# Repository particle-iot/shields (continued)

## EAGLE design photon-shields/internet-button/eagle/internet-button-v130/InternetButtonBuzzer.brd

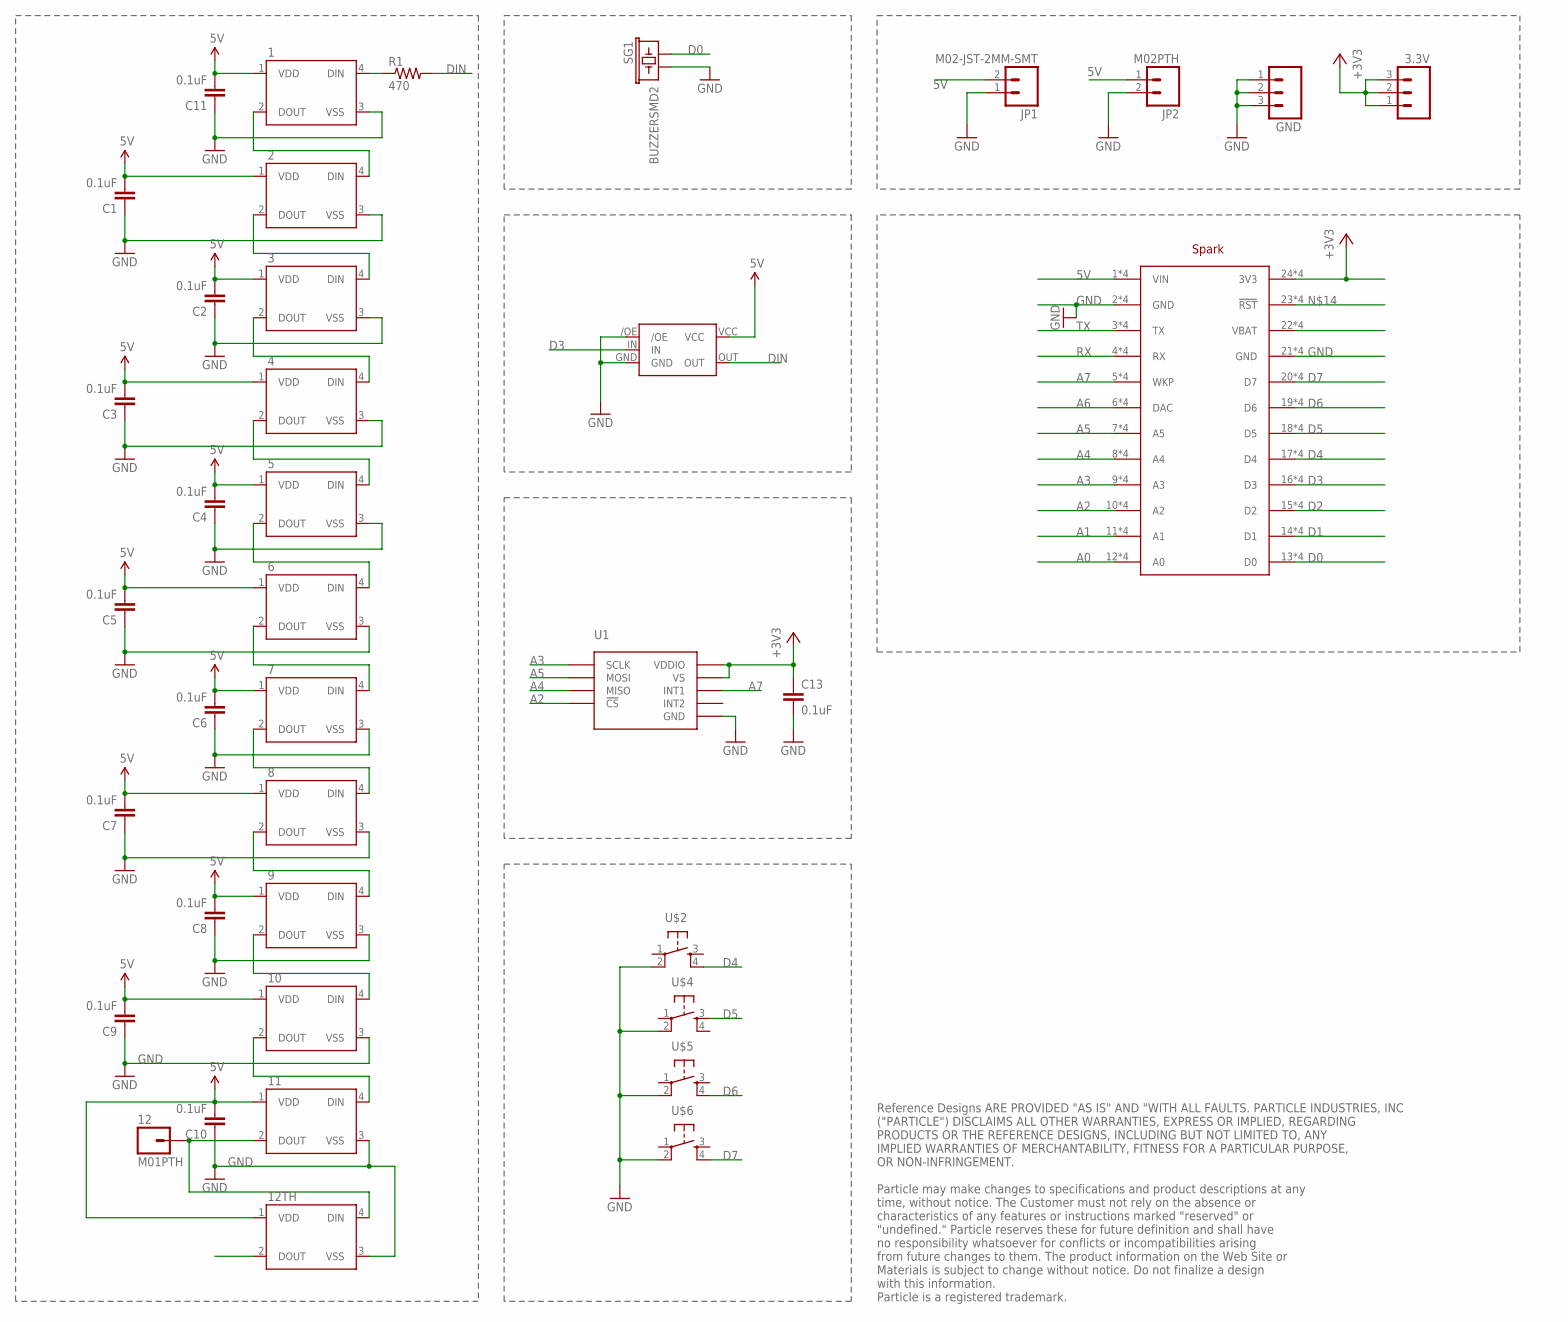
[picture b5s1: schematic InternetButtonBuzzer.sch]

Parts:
1, 2, 3, 4, 5, 6, 7, 8, 9, 10, 11: WS2812B
3.3V: M03LOCK_NO_SILK; 1X03_LOCK_NO_SILK
12: M01PTH; 1X01
12TH: WS2812B; NOCREAM_WS2812B
C1, C2, C3, C4, C5, C6, C7, C8, C9, C10, C11, C13: 0.1uF; 0603-CAP
GND: M03LOCK_NO_SILK; 1X03_LOCK_NO_SILK
JP1: M02-JST-2MM-SMT; JST-2-SMD
JP2: M02PTH; 1X02
R1: 470; 0603-RES
SG1: BUZZERSMD2; BUZZER-CCV
U1: ADXL362ADXL362-1:1; ADXL362-1:1
U$2, U$4, U$5, U$6: 12MM_TACTILE_SWITCH
U$3: SPARK_LOGO_WITH_PLANE; SPARK_LOGO_PLUS_PLANE
U$7: SPARK_COREDUAL_HEADER; SPARK_CORE_DUAL_HEADER
U$8: NL17SZ125SOT553; SOT-553

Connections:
5V: 1.1 (VDD), 2.1 (VDD), 3.1 (VDD), 4.1 (VDD), 5.1 (VDD), 6.1 (VDD), 7.1 (VDD), 8.1 (VDD), 9.1 (VDD), 10.1 (VDD), 11.1 (VDD), 12TH.1 (VDD), C1.2, C2.2, C3.2, C4.2, C5.2, C6.2, C7.2, C8.2, C9.2, C10.2, C11.2, JP1.2 (1), JP2.1, U$7.1 (VIN), U$7.1B (VIN), U$7.@1 (VIN), U$7.@1B (VIN), U$8.VCC
+3V3: 3.3V.1, 3.3V.2, 3.3V.3, C13.1, U1.P$1 (VDDIO), U1.P$14 (VS), U$7.24 (3V3), U$7.24B (3V3), U$7.@24 (3V3), U$7.@24B (3V3)
A0: U$7.12 (A0), U$7.12B (A0), U$7.@12 (A0), U$7.@12B (A0)
A1: U$7.11 (A1), U$7.11B (A1), U$7.@11 (A1), U$7.@11B (A1)
A2: U1.P$8 (!CS), U$7.10 (A2), U$7.10B (A2), U$7.@10 (A2), U$7.@10B (A2)
A3: U1.P$4 (SCLK), U$7.9 (A3), U$7.9B (A3), U$7.@9 (A3), U$7.@9B (A3)
A4: U1.P$7 (MISO), U$7.8 (A4), U$7.8B (A4), U$7.@8 (A4), U$7.@8B (A4)
A5: U1.P$6 (MOSI), U$7.7 (A5), U$7.7B (A5), U$7.@7 (A5), U$7.@7B (A5)
A6: U$7.6 (DAC), U$7.6B (DAC), U$7.@6 (DAC), U$7.@6B (DAC)
A7: U1.P$11 (INT1), U$7.5 (WKP), U$7.5B (WKP), U$7.@5 (WKP), U$7.@5B (WKP)
D0: SG1.+ (1), U$7.13 (D0), U$7.13B (D0), U$7.@13 (D0), U$7.@13B (D0)
D1: U$7.14 (D1), U$7.14B (D1), U$7.@14 (D1), U$7.@14B (D1)
D2: U$7.15 (D2), U$7.15B (D2), U$7.@15 (D2), U$7.@15B (D2)
D3: U$7.16 (D3), U$7.16B (D3), U$7.@16 (D3), U$7.@16B (D3), U$8.IN
D4: U$2.4, U$7.17 (D4), U$7.17B (D4), U$7.@17 (D4), U$7.@17B (D4)
D5: U$4.3, U$7.18 (D5), U$7.18B (D5), U$7.@18 (D5), U$7.@18B (D5)
D6: U$5.4, U$7.19 (D6), U$7.19B (D6), U$7.@19 (D6), U$7.@19B (D6)
D7: U$6.4, U$7.20 (D7), U$7.20B (D7), U$7.@20 (D7), U$7.@20B (D7)
DIN: R1.2, U$8.OUT
GND: 1.3 (VSS), 2.3 (VSS), 3.3 (VSS), 4.3 (VSS), 5.3 (VSS), 6.3 (VSS), 7.3 (VSS), 8.3 (VSS), 9.3 (VSS), 10.3 (VSS), 11.3 (VSS), 12TH.3 (VSS), C1.1, C2.1, C3.1, C4.1, C5.1, C6.1, C7.1, C8.1, C9.1, C10.1, C11.1, C13.2, GND.1, GND.2, GND.3, JP1.1 (2), JP2.2, SG1.- (2), U1.P$12 (GND), U1.P$13 (GND), U1.P$16 (GND), U$2.2, U$4.2, U$5.2, U$6.2, U$7.2 (GND), U$7.2B (GND), U$7.21 (GND), U$7.21B (GND), U$7.@2 (GND), U$7.@2B (GND), U$7.@21 (GND), U$7.@21B (GND), U$8./OE, U$8.GND
unnamed: 2.2 (DOUT), 3.4 (DIN)
unnamed: 3.2 (DOUT), 4.4 (DIN)
unnamed: 11.2 (DOUT), 12.1, 12TH.4 (DIN)
unnamed: 7.2 (DOUT), 8.4 (DIN)
unnamed: 8.2 (DOUT), 9.4 (DIN)
unnamed: 9.2 (DOUT), 10.4 (DIN)
unnamed: 10.2 (DOUT), 11.4 (DIN)
unnamed: U$7.23 (!RST), U$7.23B (!RST), U$7.@23 (!RST), U$7.@23B (!RST)
unnamed: U$7.22 (VBAT), U$7.22B (VBAT), U$7.@22 (VBAT), U$7.@22B (VBAT)
unnamed: 1.4 (DIN), R1.1
unnamed: 4.2 (DOUT), 5.4 (DIN)
unnamed: 5.2 (DOUT), 6.4 (DIN)
unnamed: 6.2 (DOUT), 7.4 (DIN)
unnamed: 1.2 (DOUT), 2.4 (DIN)
RX: U$7.4 (RX), U$7.4B (RX), U$7.@4 (RX), U$7.@4B (RX)
TX: U$7.3 (TX), U$7.3B (TX), U$7.@3 (TX), U$7.@3B (TX)

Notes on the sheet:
Reference Designs ARE PROVIDED "AS IS" AND "WITH ALL FAULTS. PARTICLE INDUSTRIES, INC ("PARTICLE") DISCLAIMS ALL OTHER WARRANTIES, EXPRESS OR IMPLIED, REGARDING PRODUCTS OR THE REFERENCE DESIGNS, INCLUDING BUT NOT LIMITED TO, ANY IMPLIED WARRANTIES OF MERCHANTABILITY, FITNESS FOR A PARTICULAR PURPO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

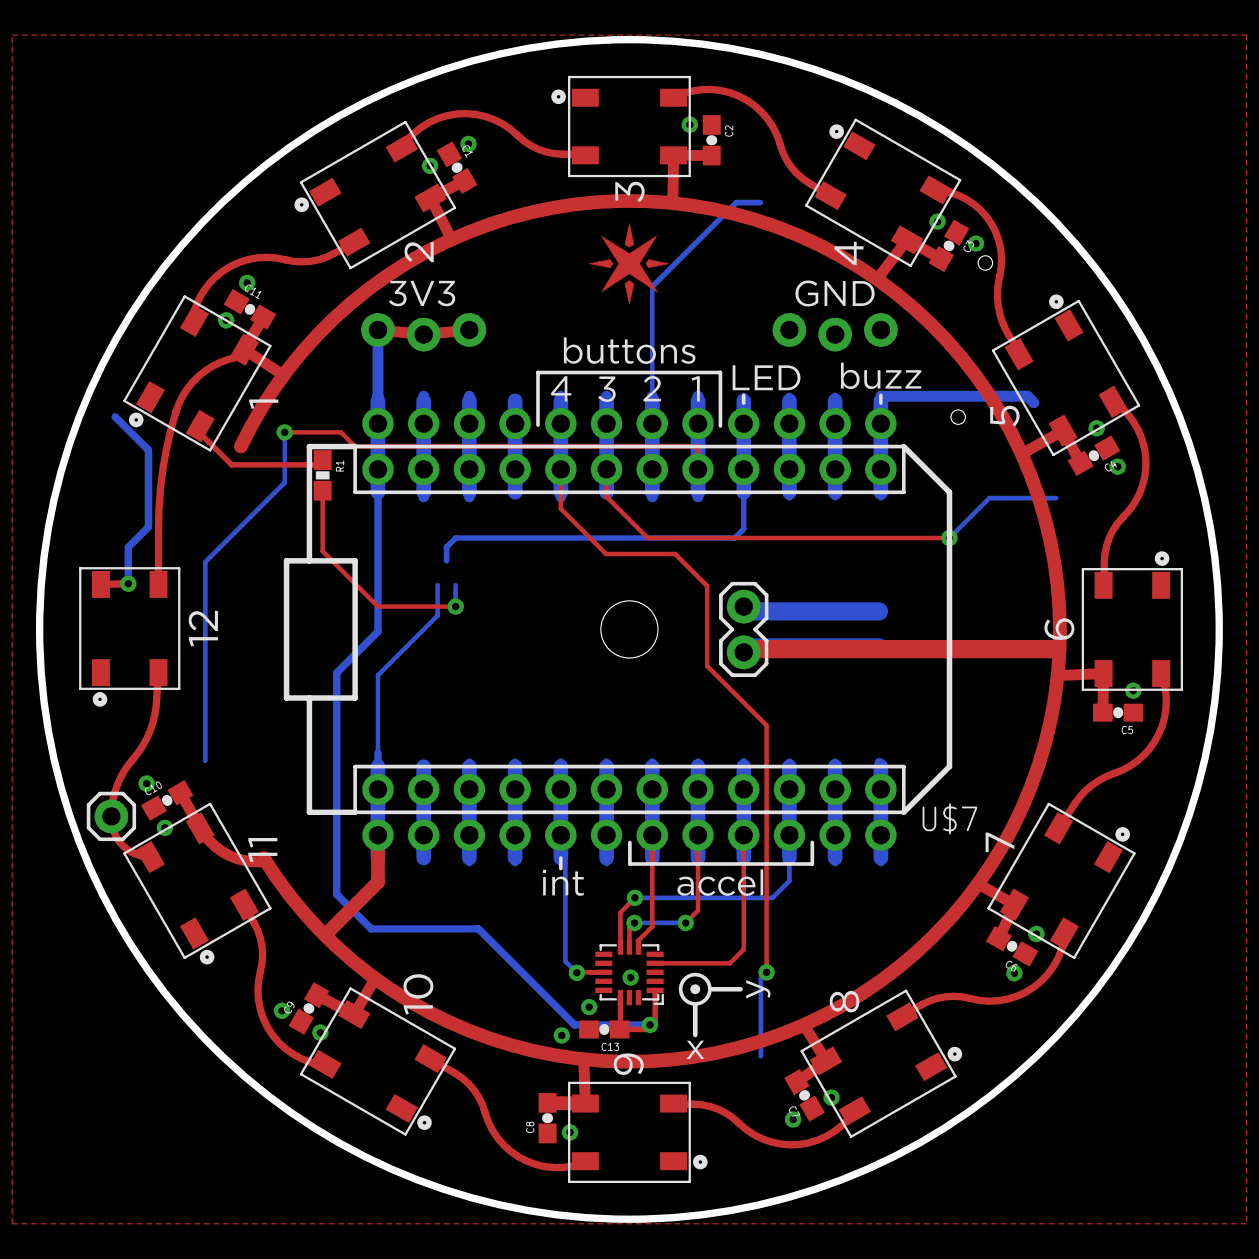
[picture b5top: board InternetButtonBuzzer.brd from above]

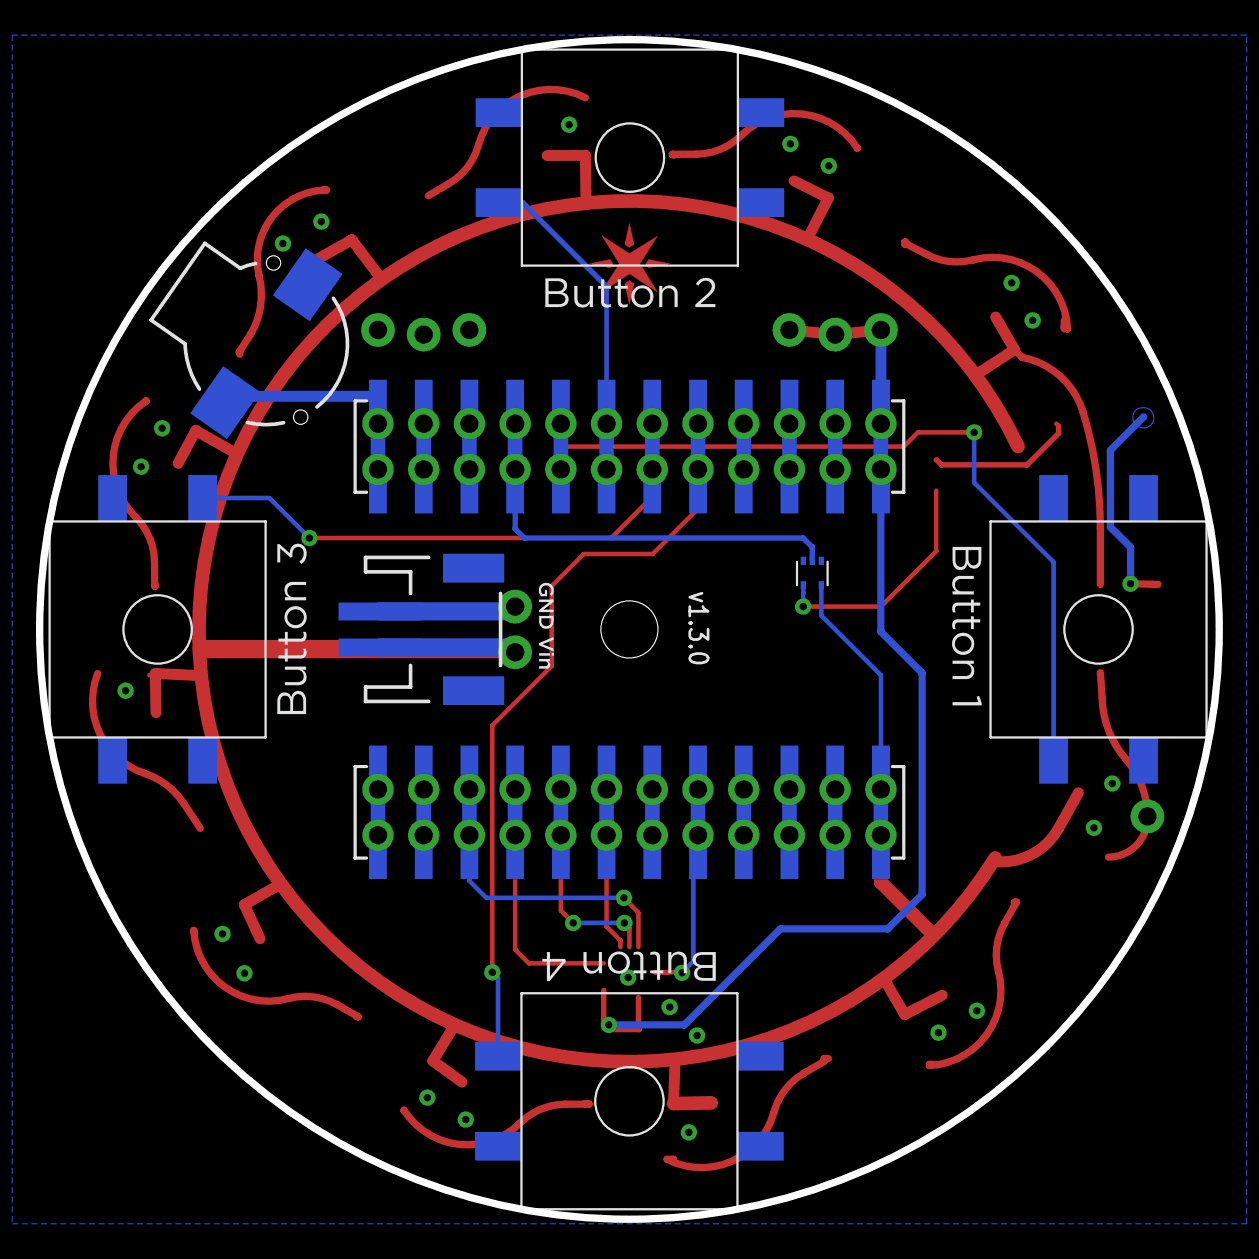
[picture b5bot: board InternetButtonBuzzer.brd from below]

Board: 2 copper layers, 65.5 x 65.5 mm, 39 parts (7 on the bottom side), 36 nets.

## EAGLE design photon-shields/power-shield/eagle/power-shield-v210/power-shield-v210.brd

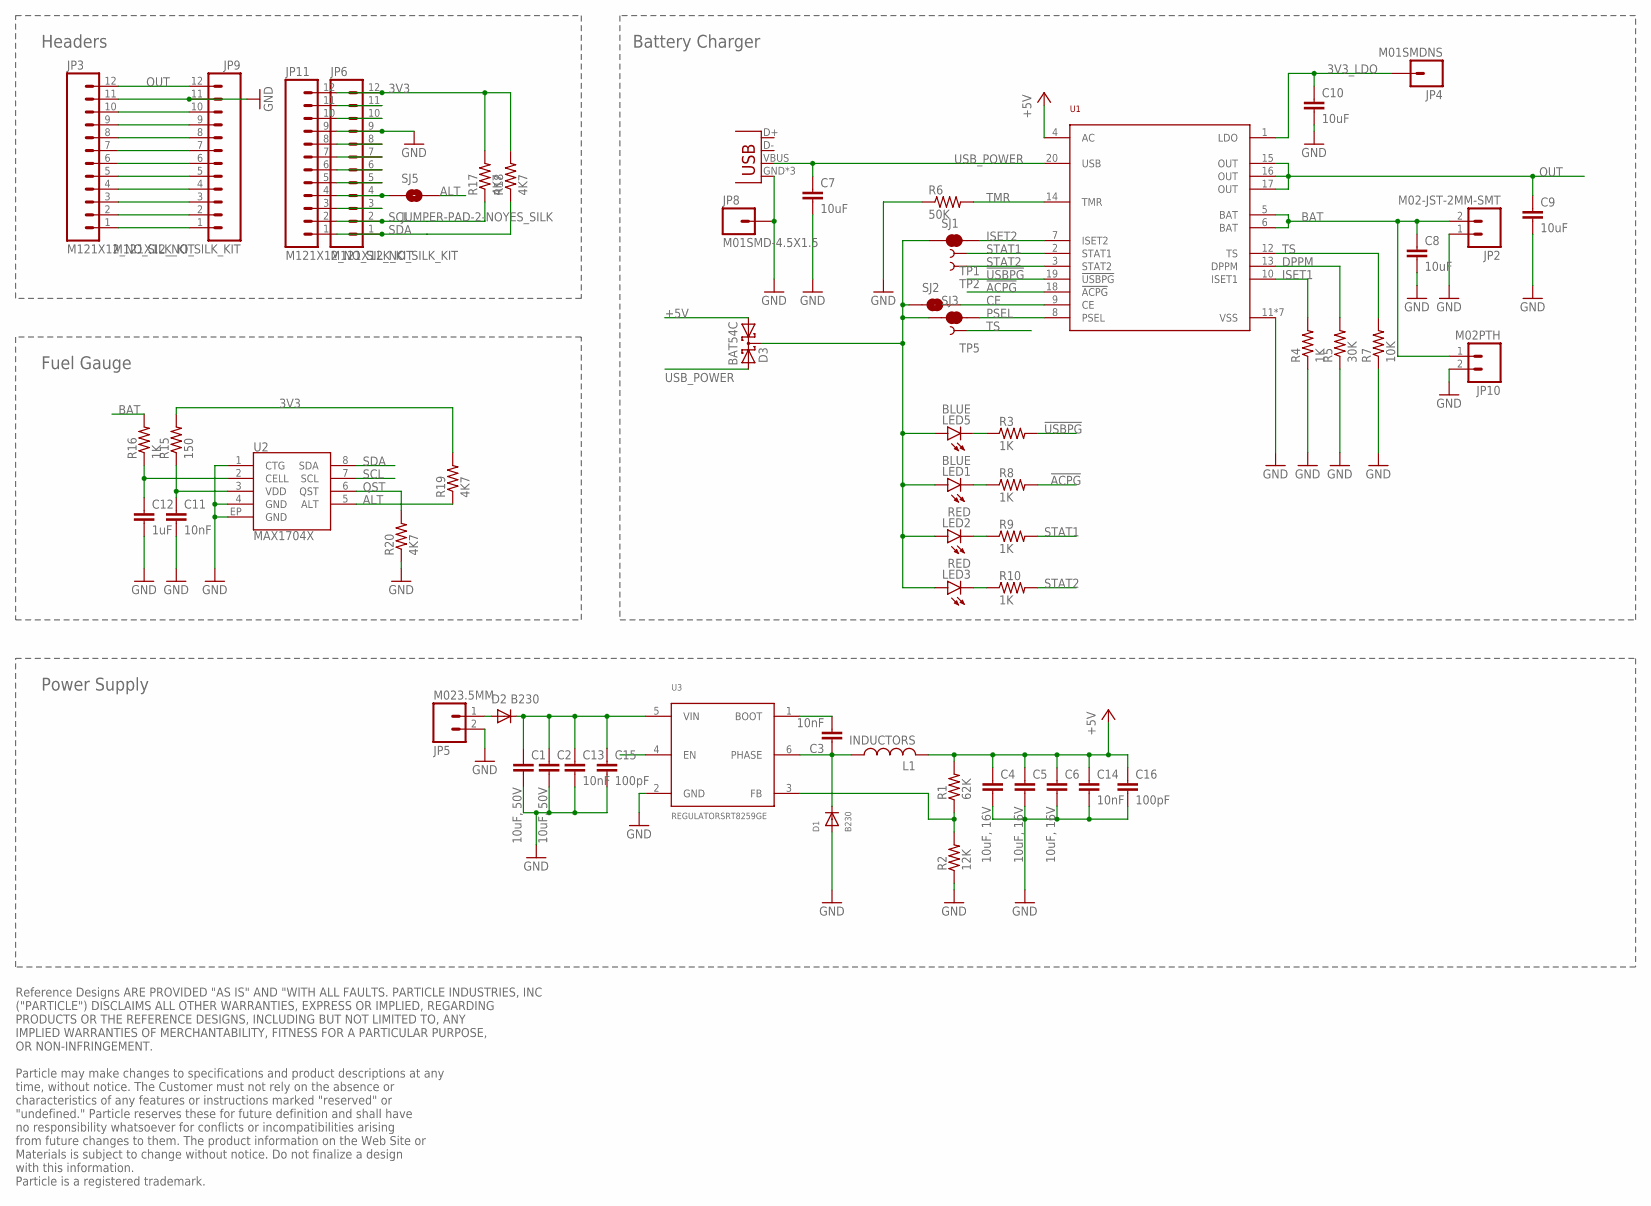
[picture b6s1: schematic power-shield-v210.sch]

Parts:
C1, C2: 10uF, 50V; 1206
C3, C11, C13, C14: 10nF; 0402-CAP
C4, C5, C6: 10uF, 16V; 1206
C7, C8, C9, C10: 10uF; 0603-CAP
C12: 1uF; 0402-CAP
C15, C16: 100pF; 0402-CAP
D1, D2: B230; SMADIODE
D3: BAT54C; SOT23
JP1: USBUSB-MICROB-SLOT-HOLE; USB-MICROB-SLOT-HOLE
JP2: M02-JST-2MM-SMT; JST-2-SMD
JP3, JP6, JP9, JP11: M121X12_NO_SILK_KIT; 1X12_NO_SILK_KIT
JP4: M01SMDNS; 1X01NS
JP5: M023.5MM; SCREWTERMINAL-3.5MM-2
JP8: M01SMD-4.5X1.5; PAD-1.5X4.5
JP10: M02PTH; 1X02
L1: INDUCTORS; NR8040T6R8N
LED1, LED5: BLUE; LED-0603
LED2, LED3: RED; LED-0603
R1: 62K; 0603-RES
R2: 12K; 0603-RES
R3, R4, R8, R9, R10: 1K; 0402-RES
R5: 30K; 0402-RES
R6: 50K; 0402-RES
R7: 10K; 0402-RES
R15: 150; 0603-RES
R16: 1K; 0603-RES
R17, R18, R19, R20: 4K7; 0402-RES
SJ1, SJ2, SJ3: JUMPER-PAD-2-NC_BY_TRACE; PAD-JUMPER-2-NC_BY_TRACE_YES_SILK
SJ5: JUMPER-PAD-2-NOYES_SILK; PAD-JUMPER-2-NO_YES_SILK
TP1, TP2, TP5: TEST-POINT3; PAD.03X.03
U1: BQ24030BQ24030; R-PVQFN-N20
U2: MAX1704X; TDFN-8
U3: REGULATORSRT8259GE; SOT23-6

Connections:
3V3: JP6.12, JP11.12, R15.2, R17.2, R18.2, R19.2
3V3_LDO: C10.1, JP4.1, U1.1 (LDO)
!ACPG: R8.2, U1.18 (!ACPG)
!USBPG: R3.2, U1.19 (!USBPG)
+5V: C4.1, C5.1, C6.1, C14.1, C16.1, D3.1 (A1), L1.P$2 (2), R1.2, U1.4 (AC)
ALT: R19.1, SJ5.2, U2.5 (ALT)
BAT: C8.1, JP2.2 (1), JP10.1, R16.2, U1.5 (BAT), U1.6 (BAT)
CE: SJ2.2, U1.9 (CE)
DPPM: R5.2, U1.13 (DPPM)
GND: C1.2, C2.2, C4.2, C5.2, C6.2, C7.2, C8.2, C9.2, C10.2, C11.2, C12.2, C13.2, C14.2, C15.2, C16.2, D1.A, JP1.GND, JP1.MT1 (GND), JP1.MT2 (GND), JP2.1 (2), JP3.11, JP5.2, JP6.9, JP8.P$1, JP9.11, JP10.2, JP11.9, R2.1, R4.1, R5.1, R6.1, R7.1, R20.1, U1.11 (VSS), U1.21 (VSS), U1.22 (VSS), U1.23 (VSS), U1.24 (VSS), U1.25 (VSS), U1.26 (VSS), U2.1 (CTG), U2.4 (GND), U2.EP (GND), U3.2 (GND)
ISET1: R4.2, U1.10 (ISET1)
ISET2: SJ1.2, U1.7 (ISET2)
unnamed: LED5.C, R3.1
unnamed: D3.3 (CC), LED1.A, LED2.A, LED3.A, LED5.A, SJ1.1, SJ2.1, SJ3.1
unnamed: LED3.C, R10.1
unnamed: LED2.C, R9.1
unnamed: LED1.C, R8.1
unnamed: JP6.4, JP11.4, SJ5.1
unnamed: JP3.1, JP9.1
unnamed: JP3.2, JP9.2
unnamed: JP3.3, JP9.3
unnamed: C12.1, R16.1, U2.2 (CELL)
unnamed: C11.1, R15.1, U2.3 (VDD)
unnamed: JP3.4, JP9.4
unnamed: C1.1, C2.1, C13.1, C15.1, D2.C, U3.5 (VIN)
unnamed: JP3.5, JP9.5
unnamed: JP3.6, JP9.6
unnamed: JP3.7, JP9.7
unnamed: JP3.8, JP9.8
unnamed: JP3.9, JP9.9
unnamed: JP3.10, JP9.10
unnamed: JP6.11, JP11.11
unnamed: JP6.10, JP11.10
unnamed: JP6.8, JP11.8
unnamed: JP6.7, JP11.7
unnamed: JP6.6, JP11.6
unnamed: JP6.5, JP11.5
unnamed: JP6.3, JP11.3
unnamed: D2.A, JP5.1
unnamed: C3.1, D1.C, L1.P$1 (1), U3.6 (PHASE)
unnamed: C3.2, U3.1 (BOOT)
unnamed: R1.1, R2.2, U3.3 (FB)
OUT: C9.1, JP3.12, JP9.12, U1.15 (OUT), U1.16 (OUT), U1.17 (OUT)
PSEL: SJ3.2, U1.8 (PSEL)
QST: R20.2, U2.6 (QST)
SCL: JP6.2, JP11.2, R17.1, U2.7 (SCL)
SDA: JP6.1, JP11.1, R18.1, U2.8 (SDA)
STAT1: R9.2, TP1.P$1, U1.2 (STAT1)
STAT2: R10.2, TP2.P$1, U1.3 (STAT2)
TMR: R6.2, U1.14 (TMR)
TS: R7.2, TP5.P$1, U1.12 (TS)
USB_POWER: C7.1, D3.2 (A2), JP1.VBUS, U1.20 (USB)

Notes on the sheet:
Power Supply
Headers
Fuel Gauge
Battery Charger
Reference Designs ARE PROVIDED "AS IS" AND "WITH ALL FAULTS. PARTICLE INDUSTRIES, INC ("PARTICLE") DISCLAIMS ALL OTHER WARRANTIES, EXPRESS OR IMPLIED, REGARDING PRODUCTS OR THE REFERENCE DESIGNS, INCLUDING BUT NOT LIMITED TO, ANY IMPLIED WARRANTIES OF MERCHANTABILITY, FITNESS FOR A PARTICULAR PURPO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

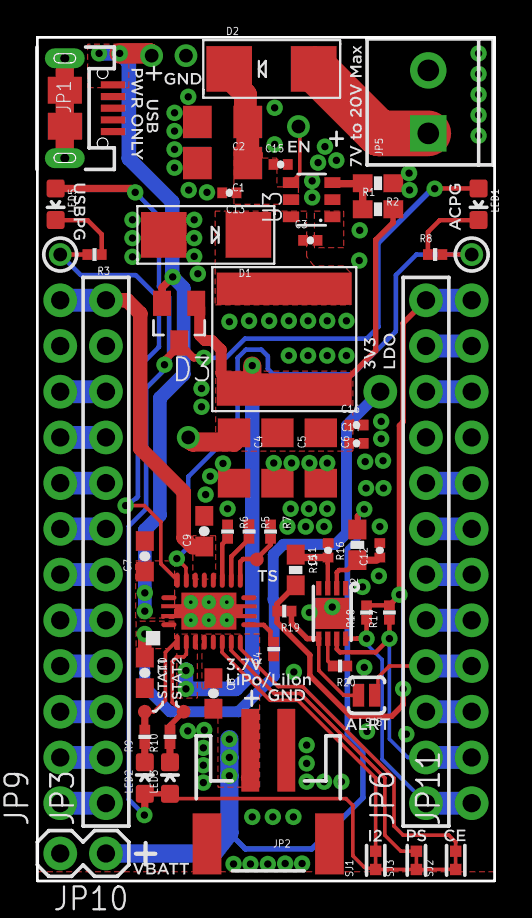
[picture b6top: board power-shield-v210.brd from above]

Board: 2 copper layers, 25.4 x 46.9 mm, 60 parts (1 on the bottom side), 52 nets.

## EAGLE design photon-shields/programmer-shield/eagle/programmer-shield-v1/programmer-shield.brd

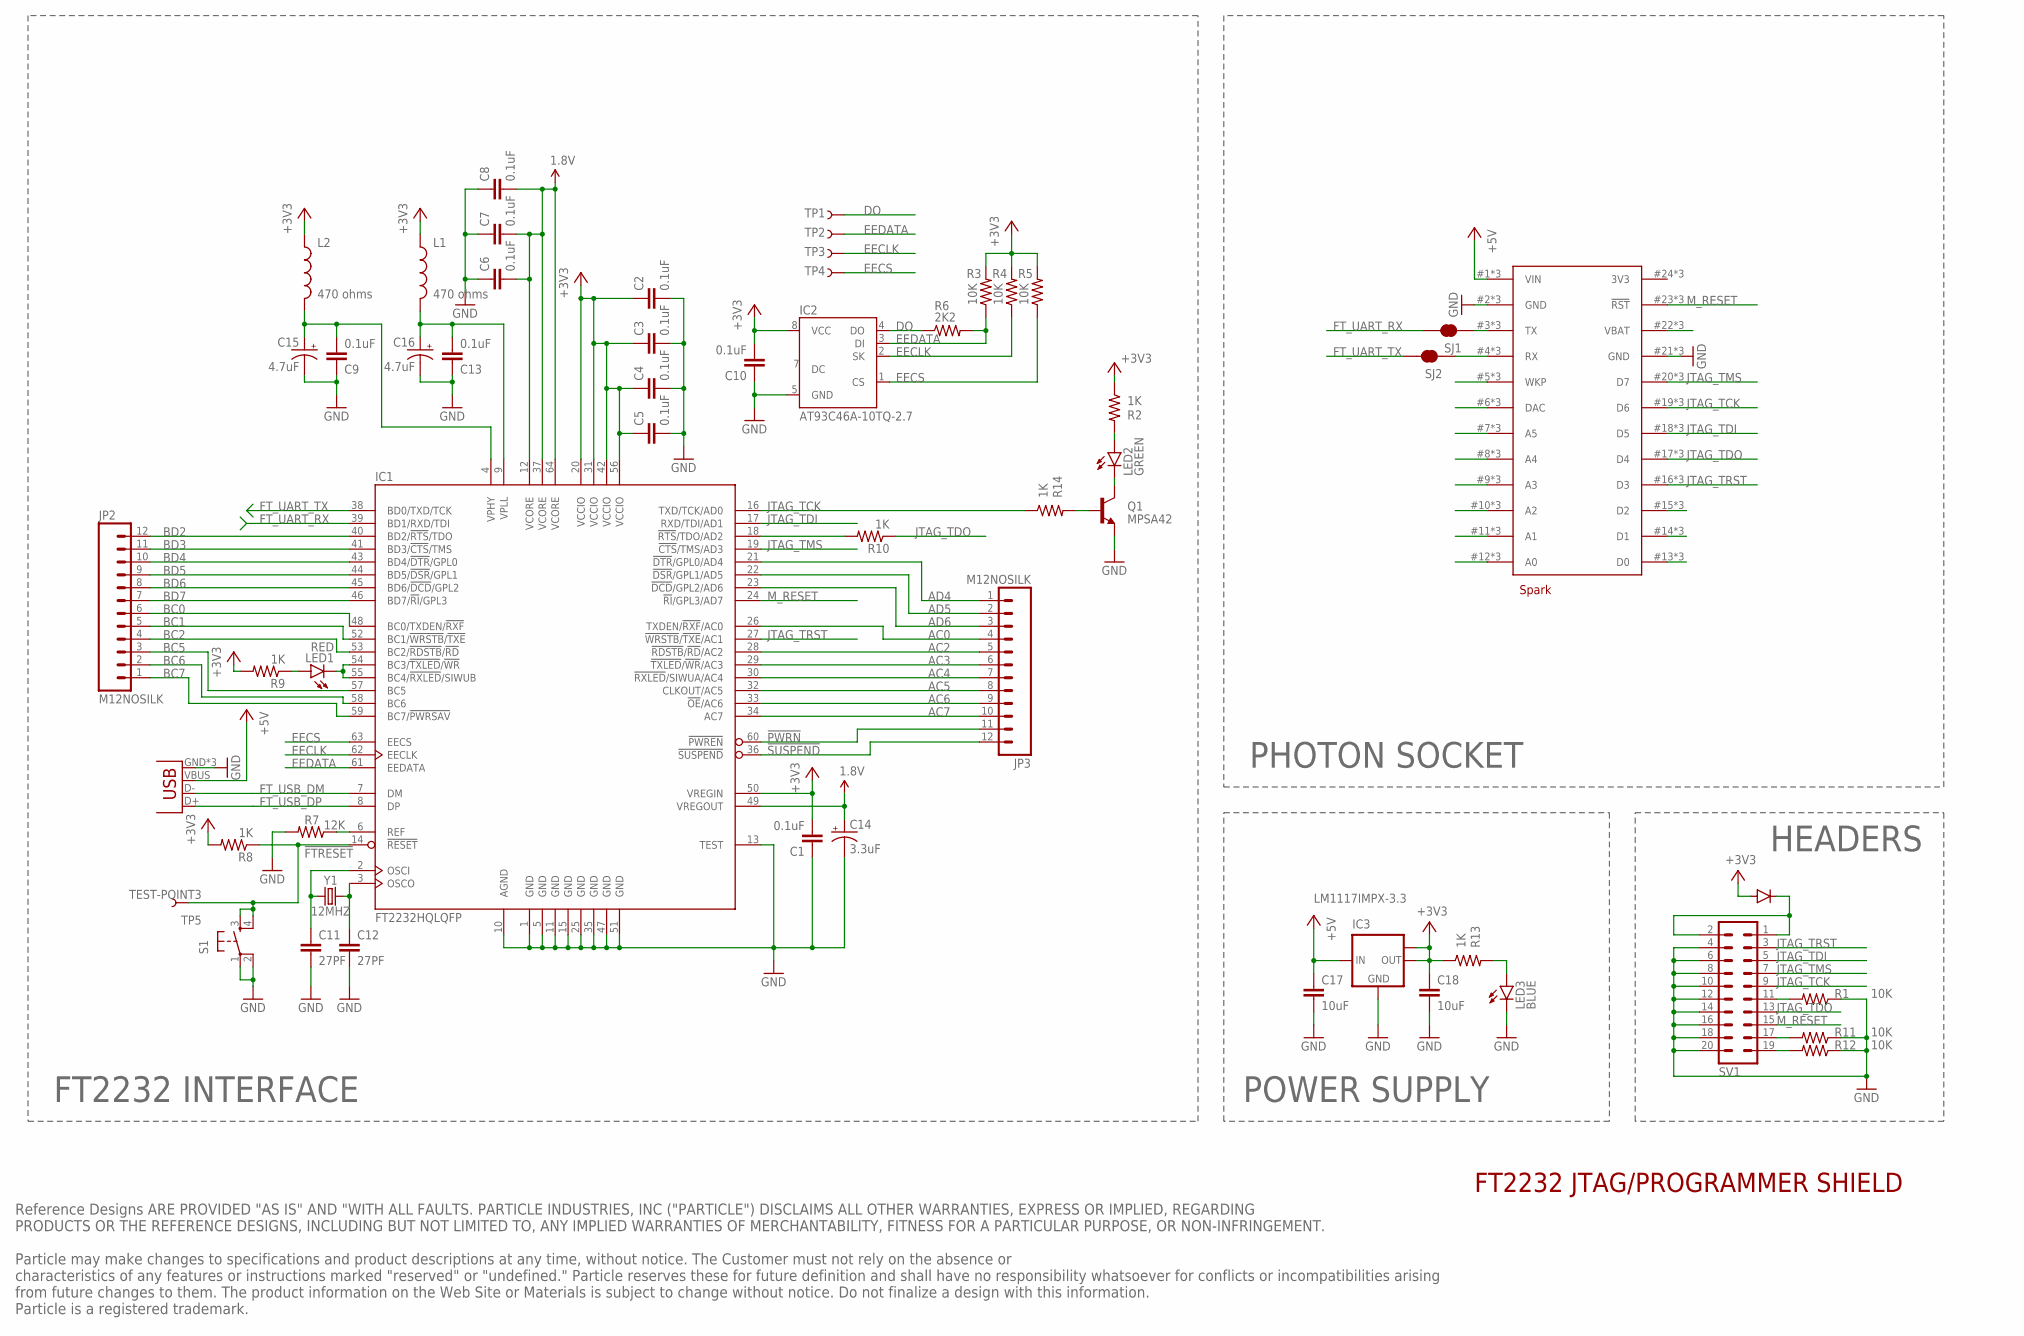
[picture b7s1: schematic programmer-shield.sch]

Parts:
C1, C2, C3, C4, C5, C6, C7, C8, C9, C10, C13: 0.1uF; 0603-CAP
C11, C12: 27PF; 0603-CAP
C14: 3.3uF; EIA3216
C15, C16: 4.7uF; EIA3216
C17, C18: 10uF; 0603-CAP
D1: DIODE; DIODE-DO-220AA(SMP)
IC1: FT2232HQLQFP; TQFP64-10X10
IC2: AT93C46A-10TQ-2.7; TSSOP8
IC3: LM1117IMPX-3.3; SOT223
JP1: USBUSB-MICROB-SLOT-HOLE; USB-MICROB-SLOT-HOLE
JP2, JP3: M12NOSILK; 1X12-SMALL-PADS-NO-SILK
L1, L2: 470 ohms; 0603
LED1: RED; LED-0603
LED2: GREEN; LED-0603
LED3: BLUE; LED-0603
Q1: MPSA42; SOT23
R1, R3, R4, R5, R11, R12: 10K; 0603-RES
R2, R8, R9, R10, R13, R14: 1K; 0603-RES
R6: 2K2; 0603-RES
R7: 12K; 0603-RES
S1: TAC_SWITCHSMD; TACTILE_SWITCH_SMD
SJ1, SJ2: JUMPER-PAD-2-NC_BY_TRACE; PAD-JUMPER-2-NC_BY_TRACE_YES_SILK
SV1: ML20
TP1, TP2, TP3, TP4, TP5: TEST-POINT3; PAD.03X.03
U$1: SPARK_LOGO; SPARK_LOGO_TSTOP
U$3: SPARK_CORE; SPARK_CORE_STACKABLE
Y1: 12MHZ; CRYSTAL-TXC-7A

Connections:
1.8V: C6.2, C7.2, C8.2, C14.A (+), IC1.12 (VCORE), IC1.37 (VCORE), IC1.49 (VREGOUT), IC1.64 (VCORE)
3V3: U$3.24 (3V3), U$3.#24 (3V3), U$3.@24 (3V3)
!FTRESET: IC1.14 (!RESET), R8.1, S1.3, S1.4, TP5.P$1
!PWRN: IC1.60 (!PWREN), JP3.11
!SUSPEND: IC1.36 (!SUSPEND), JP3.12
+3V3: C1.2, C2.1, C3.1, C4.1, C5.1, C10.2, C18.1, D1.ANODE, IC1.20 (VCCIO), IC1.31 (VCCIO), IC1.42 (VCCIO), IC1.50 (VREGIN), IC1.56 (VCCIO), IC2.8 (VCC), IC3.2 (OUT), IC3.TAB (OUT1), L1.1, L2.1, R2.1, R3.2, R4.2, R5.2, R8.2, R9.2, R13.1
+5V: C17.1, IC3.3 (IN), JP1.VBUS, U$3.1 (VIN), U$3.#1 (VIN), U$3.@1 (VIN)
AC0: IC1.26 (TXDEN/!RXF!/AC0), JP3.4
AC2: IC1.28 (!RDSTB!/!RD!/AC2), JP3.5
AC3: IC1.29 (!TXLED!/!WR!/AC3), JP3.6
AC4: IC1.30 (!RXLED!/SIWUA/AC4), JP3.7
AC5: IC1.32 (CLKOUT/AC5), JP3.8
AC6: IC1.33 (!OE!/AC6), JP3.9
AC7: IC1.34 (AC7), JP3.10
AD4: IC1.21 (!DTR!/GPL0/AD4), JP3.1
AD5: IC1.22 (!DSR!/GPL1/AD5), JP3.2
AD6: IC1.23 (!DCD!/GPL2/AD6), JP3.3
BC0: IC1.48 (BC0/TXDEN/!RXF), JP2.6
BC1: IC1.52 (BC1/!WRSTB!/!TXE), JP2.5
BC2: IC1.53 (BC2/!RDSTB!/!RD), JP2.4
BC5: IC1.57 (BC5), JP2.3
BC6: IC1.58 (BC6), JP2.2
BC7: IC1.59 (BC7/!PWRSAV), JP2.1
BD2: IC1.40 (BD2/!RTS!/TDO), JP2.12
BD3: IC1.41 (BD3/!CTS!/TMS), JP2.11
BD4: IC1.43 (BD4/!DTR!/GPL0), JP2.10
BD5: IC1.44 (BD5/!DSR!/GPL1), JP2.9
BD6: IC1.45 (BD6/!DCD!/GPL2), JP2.8
BD7: IC1.46 (BD7/!RI!/GPL3), JP2.7
DO: IC2.4 (DO), R6.1, TP1.P$1
EECLK: IC1.62 (EECLK), IC2.2 (SK), R4.1, TP3.P$1
EECS: IC1.63 (EECS), IC2.1 (CS), R5.1, TP4.P$1
EEDATA: IC1.61 (EEDATA), IC2.3 (DI), R3.1, R6.2, TP2.P$1
FT_UART_RX: IC1.39 (BD1/RXD/TDI), SJ1.2
FT_UART_TX: IC1.38 (BD0/TXD/TCK), SJ2.2
FT_USB_DM: IC1.7 (DM), JP1.D-
FT_USB_DP: IC1.8 (DP), JP1.D+
GND: C1.1, C2.2, C3.2, C4.2, C5.2, C6.1, C7.1, C8.1, C9.1, C10.1, C11.2, C12.2, C13.1, C14.C (-), C15.C (-), C16.C (-), C17.2, C18.2, IC1.1 (GND), IC1.5 (GND), IC1.10 (AGND), IC1.11 (GND), IC1.13 (TEST), IC1.15 (GND), IC1.25 (GND), IC1.35 (GND), IC1.47 (GND), IC1.51 (GND), IC2.5 (GND), IC3.1 (GND), JP1.GND, JP1.MT1 (GND), JP1.MT2 (GND), LED3.C, Q1.2 (E), R1.1, R7.2, R11.1, R12.1, S1.1, S1.2, SV1.4, SV1.6, SV1.8, SV1.10, SV1.12, SV1.14, SV1.16, SV1.18, SV1.20, U$3.2 (GND), U$3.21 (GND), U$3.#2 (GND), U$3.#21 (GND), U$3.@2 (GND), U$3.@21 (GND)
JTAG_TCK: IC1.16 (TXD/TCK/AD0), R14.1, SV1.9, U$3.19 (D6), U$3.#19 (D6), U$3.@19 (D6)
JTAG_TDI: IC1.17 (RXD/TDI/AD1), SV1.5, U$3.18 (D5), U$3.#18 (D5), U$3.@18 (D5)
JTAG_TDO: R10.1, SV1.13, U$3.17 (D4), U$3.#17 (D4), U$3.@17 (D4)
JTAG_TMS: IC1.19 (!CTS!/TMS/AD3), SV1.7, U$3.20 (D7), U$3.#20 (D7), U$3.@20 (D7)
JTAG_TRST: IC1.27 (!WRSTB!/!TXE!/AC1), SV1.3, U$3.16 (D3), U$3.#16 (D3), U$3.@16 (D3)
M_RESET: IC1.24 (!RI!/GPL3/AD7), SV1.15, U$3.23 (!RST), U$3.#23 (!RST), U$3.@23 (!RST)
unnamed: IC1.6 (REF), R7.1
unnamed: C13.2, C16.A (+), IC1.9 (VPLL), L1.2
unnamed: SJ1.1, U$3.3 (TX), U$3.#3 (TX), U$3.@3 (TX)
unnamed: C12.1, IC1.3 (OSCO), Y1.P$2 (2)
unnamed: C11.1, IC1.2 (OSCI), Y1.P$1 (1)
unnamed: C9.2, C15.A (+), IC1.4 (VPHY), L2.2
unnamed: IC1.54 (BC3/!TXLED!/!WR), IC1.55 (BC4/!RXLED!/SIWUB), LED1.C
unnamed: LED1.A, R9.1
unnamed: Q1.1 (B), R14.2
unnamed: U$3.22 (VBAT), U$3.#22 (VBAT), U$3.@22 (VBAT)
unnamed: U$3.15 (D2), U$3.#15 (D2), U$3.@15 (D2)
unnamed: LED3.A, R13.2
unnamed: U$3.14 (D1), U$3.#14 (D1), U$3.@14 (D1)
unnamed: U$3.13 (D0), U$3.#13 (D0), U$3.@13 (D0)
unnamed: IC1.18 (!RTS!/TDO/AD2), R10.2
unnamed: U$3.5 (WKP), U$3.#5 (WKP), U$3.@5 (WKP)
unnamed: U$3.6 (DAC), U$3.#6 (DAC), U$3.@6 (DAC)
unnamed: U$3.7 (A5), U$3.#7 (A5), U$3.@7 (A5)
unnamed: U$3.8 (A4), U$3.#8 (A4), U$3.@8 (A4)
unnamed: U$3.9 (A3), U$3.#9 (A3), U$3.@9 (A3)
unnamed: U$3.10 (A2), U$3.#10 (A2), U$3.@10 (A2)
unnamed: U$3.11 (A1), U$3.#11 (A1), U$3.@11 (A1)
unnamed: SJ2.1, U$3.4 (RX), U$3.#4 (RX), U$3.@4 (RX)
unnamed: U$3.12 (A0), U$3.#12 (A0), U$3.@12 (A0)
unnamed: D1.CATHODE, SV1.1, SV1.2
unnamed: LED2.C, Q1.3 (C)
unnamed: LED2.A, R2.2
unnamed: R1.2, SV1.11
unnamed: R11.2, SV1.17
unnamed: R12.2, SV1.19

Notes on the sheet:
FT2232 JTAG/PROGRAMMER SHIELD
FT2232 INTERFACE
POWER SUPPLY
HEADERS
PHOTON SOCKET
Reference Designs ARE PROVIDED "AS IS" AND "WITH ALL FAULTS. PARTICLE INDUSTRIES, INC ("PARTICLE") DISCLAIMS ALL OTHER WARRANTIES, EXPRESS OR IMPLIED, REGARDING PRODUCTS OR THE REFERENCE DESIGNS, INCLUDING BUT NOT LIMITED TO, ANY IMPLIED WARRANTIES OF MERCHANTABILITY, FITNESS FOR A PARTICULAR PURPO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

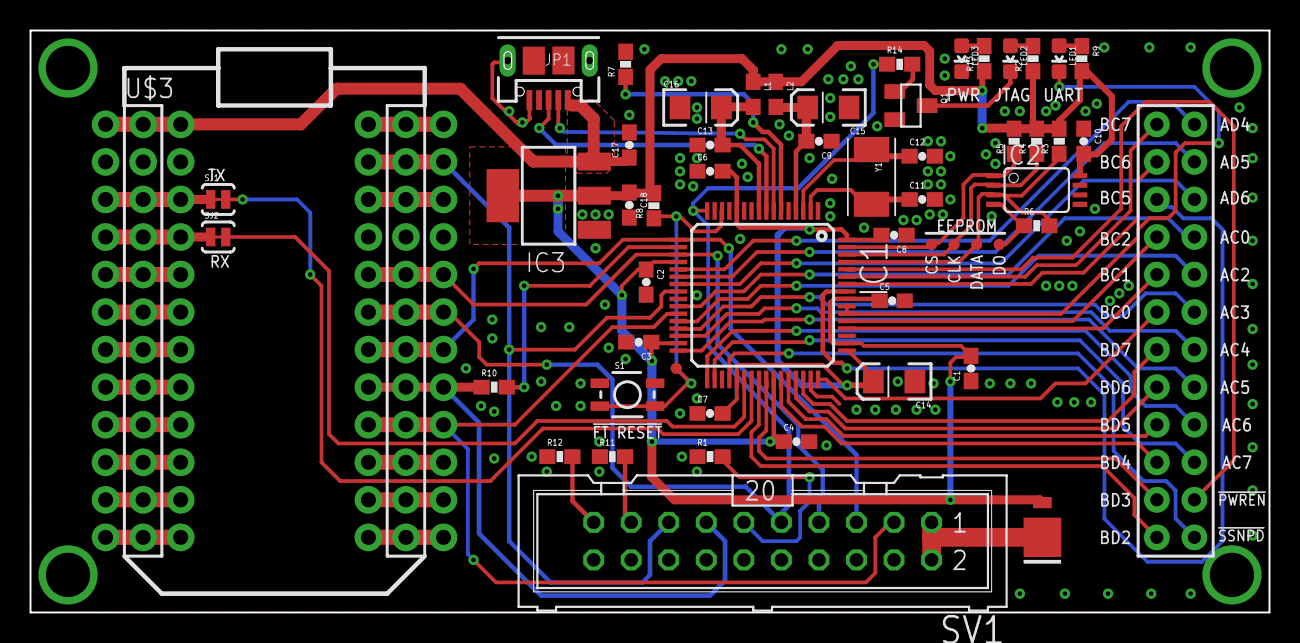
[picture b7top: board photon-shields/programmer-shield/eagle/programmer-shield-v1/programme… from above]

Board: 2 copper layers, 83.8 x 39.4 mm, 58 parts (0 on the bottom side), 74 nets.

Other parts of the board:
U$2: SPARK_LOGO2
